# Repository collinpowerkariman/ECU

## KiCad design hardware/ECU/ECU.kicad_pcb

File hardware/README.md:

# Wiring Guide
To simplify wiring we'll set a standard wire color for each functionality.

| Color  | Description      |
|--------|------------------|
| RED    | Positive voltage |
| BLACK  | Ground voltage   |
| YELLOW | SPI - CLK        |
| WHITE  | SPI - CIPO/MISO  |
| BLUE   | SPI - COPI/MOSI  |
| GREEN  | SPI - CS         |

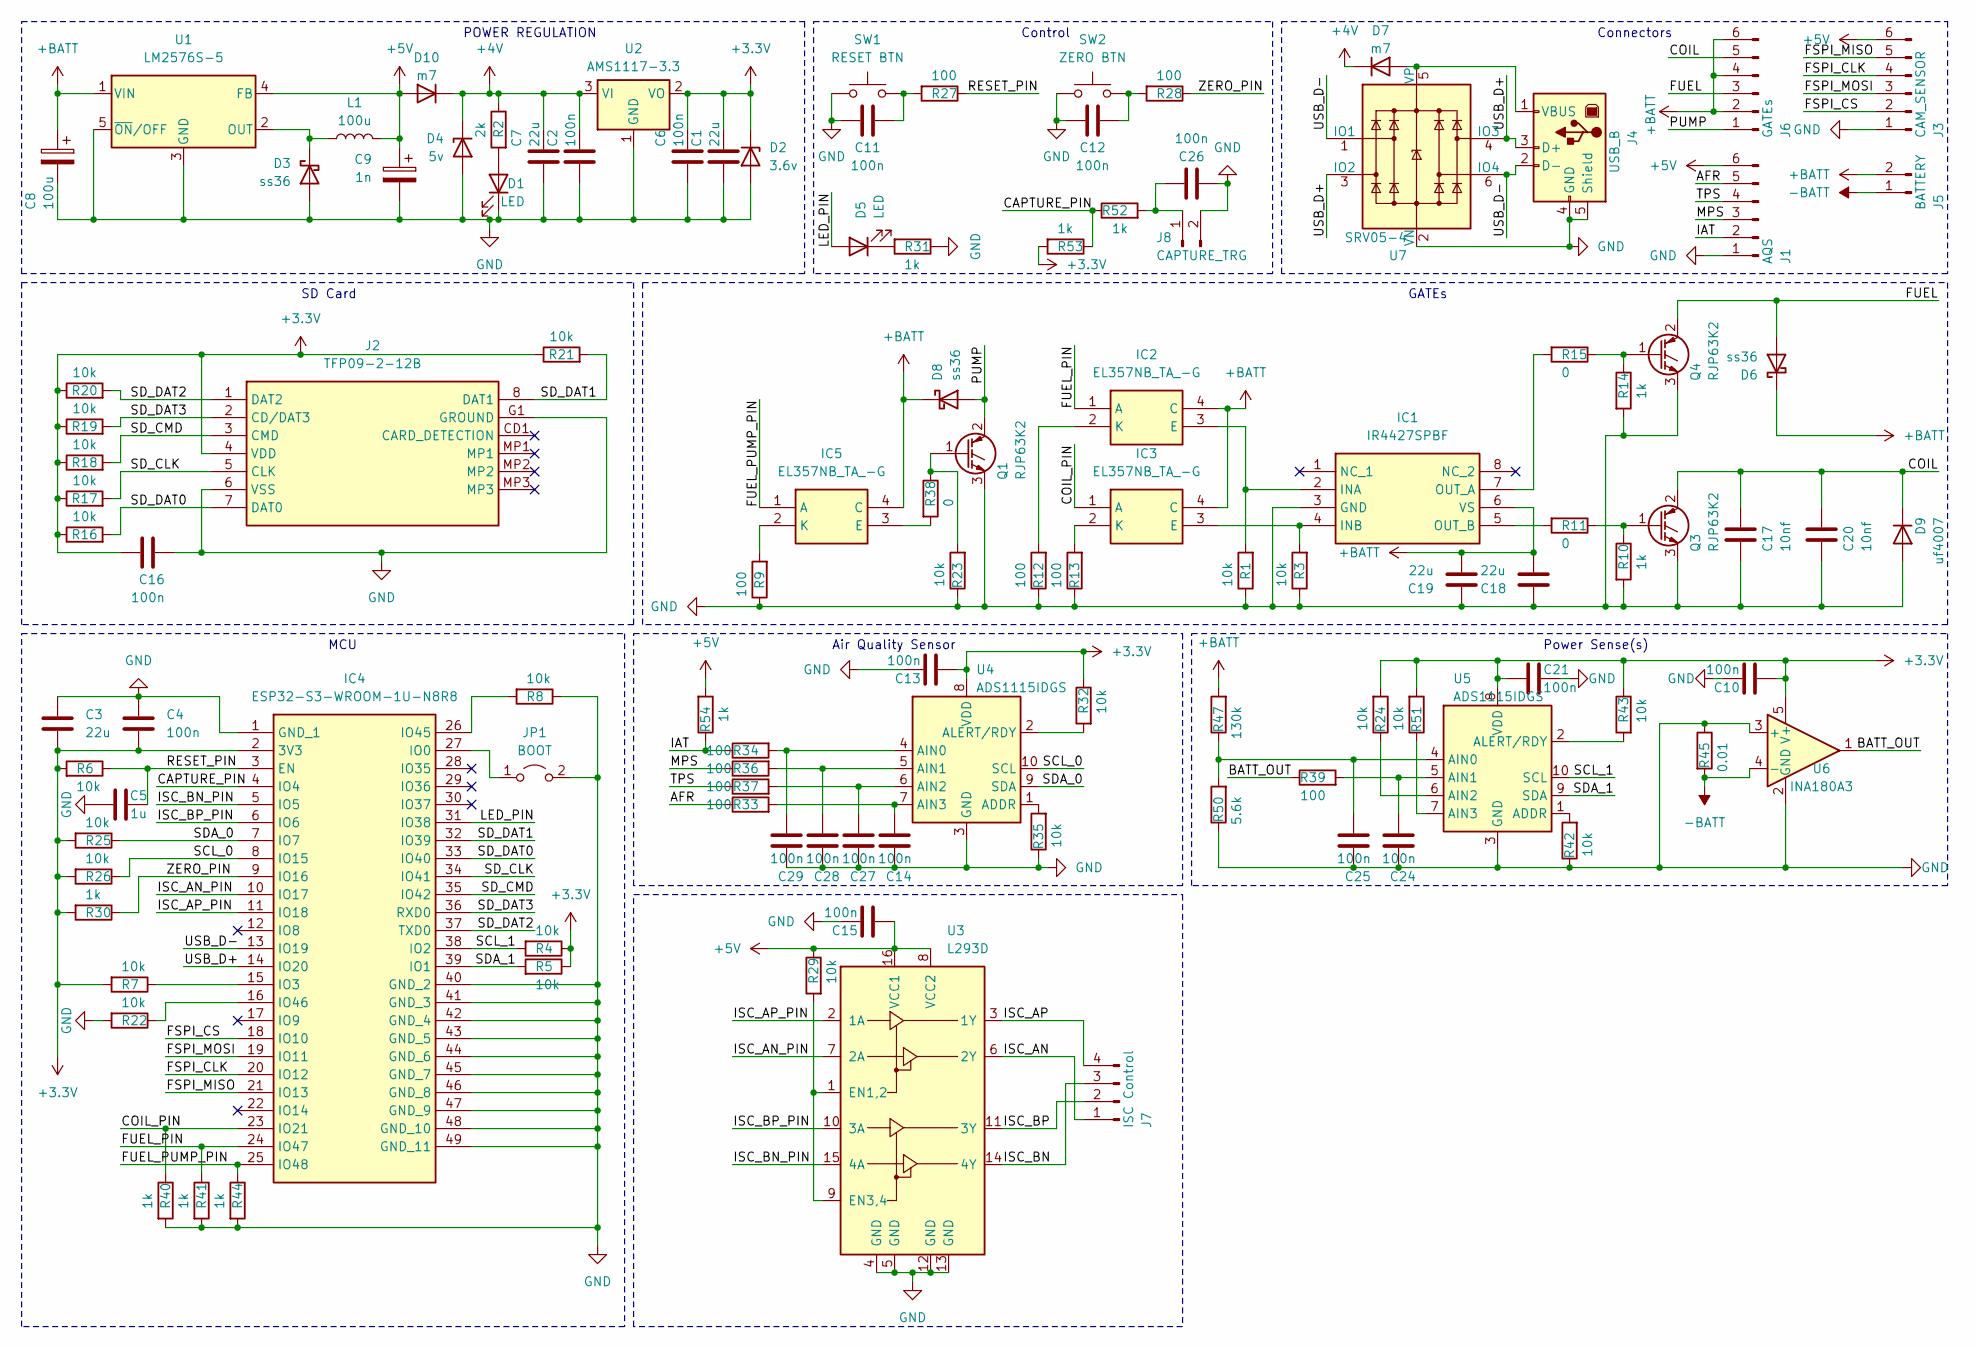
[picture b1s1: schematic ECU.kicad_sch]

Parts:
C1, C7, C18, C19: 22u; C_0805_2012Metric_Pad1.18x1.45mm_HandSolder
C2, C6: 100n; C_0805_2012Metric_Pad1.18x1.45mm_HandSolder
C3: 22u; C_0603_1608Metric
C4, C10, C11, C12, C13, C14, C15, C21, C24, C25, C26, C27, C28, C29: 100n; C_0603_1608Metric
C5: 1u; C_0603_1608Metric
C8: 100u; CP_Elec_10x10
C9: 1n; CP_Elec_10x10
C16: 100n; C_0603_1608Metric_Pad1.08x0.95mm_HandSolder
C17, C20: 10nf; C_1206_3216Metric_Pad1.33x1.80mm_HandSolder
D1, D5: LED; LED_0603_1608Metric_Pad1.05x0.95mm_HandSolder
D2: 3.6v; D_1206_3216Metric_Pad1.42x1.75mm_HandSolder
D3, D6, D8: ss36; D_SMC
D4: 5v; D_1206_3216Metric_Pad1.42x1.75mm_HandSolder
D7, D10: m7; D_SMA
D9: uf4007; D_SMA
IC1: IR4427SPBF; SOIC127P600X175-8N; Manufacturer_Part_Number IR4427SPBF; Mouser Part Number 942-IR4427SPBF
IC2, IC3, IC5: EL357NB_TA_-G; EL357NG; Manufacturer_Part_Number EL357NB(TA)-G; Mouser Part Number 638-EL357NBTAG
IC4: ESP32-S3-WROOM-1U-N8R8; ESP32S3WROOM1UN4; Manufacturer_Part_Number ESP32-S3-WROOM-1U-N8R8; Mouser Part Number 356-ESP32S3WRM1UN8R8
J1: AQS; JST_XH_B6B-XH-A_1x06_P2.50mm_Vertical
J2: TFP09-2-12B; TFP09212B; Manufacturer_Part_Number TFP09-2-12B
J3: CAM_SENSOR; JST_XH_B6B-XH-A_1x06_P2.50mm_Vertical
J4: USB_B; USB_B_TE_5787834_Vertical
J5: BATTERY; Molex_KK-396_5273-02A_1x02_P3.96mm_Vertical
J6: GATEs; Molex_KK-396_5273-06A_1x06_P3.96mm_Vertical
J7: ISC Control; JST_XH_B4B-XH-A_1x04_P2.50mm_Vertical
J8: CAPTURE_TRG; JST_XH_B2B-XH-A_1x02_P2.50mm_Vertical
JP1: BOOT; PinHeader_1x02_P2.54mm_Vertical
L1: 100u; INDPM102100X400N
Q1, Q3, Q4: RJP63K2; TO-263-2
R1, R3, R4, R5, R6, R7, R8, R22, R23, R24, R25, R26, R29, R32, R35, R42, R43, R51: 10k; R_0603_1608Metric_Pad0.98x0.95mm_HandSolder
R2: 2k; R_0603_1608Metric_Pad0.98x0.95mm_HandSolder
R9, R12, R13, R27, R28, R33, R34, R36, R37, R39: 100; R_0603_1608Metric_Pad0.98x0.95mm_HandSolder
R10, R14, R30, R31, R40, R41, R44, R52, R53, R54: 1k; R_0603_1608Metric_Pad0.98x0.95mm_HandSolder
R11, R15, R38: 0; R_0603_1608Metric_Pad0.98x0.95mm_HandSolder
R16, R17, R18, R19, R20, R21: 10k; R_0603_1608Metric
R45: 0.01; RESC10052X106N
R47: 130k; R_0603_1608Metric_Pad0.98x0.95mm_HandSolder
R50: 5.6k; R_0603_1608Metric_Pad0.98x0.95mm_HandSolder
SW1: RESET BTN; SW_SPST_PTS810
SW2: ZERO BTN; SW_SPST_PTS810
U1: LM2576S-5; TO-263-5_TabPin3
U2: AMS1117-3.3; SOT-223-3_TabPin2
U3: L293D; DIP-16_W7.62mm_SMDSocket_SmallPads
U4, U5: ADS1115IDGS; TSSOP-10_3x3mm_P0.5mm
U6: INA180A3; SOT-23-5
U7: SRV05-4; SOT-23-6

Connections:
+3.3V: C1.1, C3.2, C4.2, C6.1, C10.2, C13.2, C16.1, C21.2, D2.1 (K), IC4.2 (3V3), J2.4 (VDD), R4.1, R5.1, R6.2, R7.2, R16.1, R17.1, R18.1, R19.1, R20.1, R21.1, R24.2, R25.2, R26.2, R30.2, R32.1, R43.1, R51.2, R53.2, U2.2 (VO), U4.8 (VDD), U5.8 (VDD), U6.5 (V+)
+4V: C2.1, C7.1, D4.1 (K), D7.1 (K), D10.1 (K), R2.1, U2.3 (VI)
+5V: C9.1, C15.2, D10.2 (A), J1.6, J3.6, L1.2, R29.1, R54.2, U1.4 (FB), U3.8 (VCC2), U3.16 (VCC1)
+BATT: C8.1, C18.1, C19.1, D6.1 (K), D8.1 (K), IC1.6 (VS), IC2.4 (C), IC3.4 (C), IC5.4 (C), J5.2, J6.2, J6.4, J6.6, R47.2, U1.1 (VIN)
-BATT: J5.1, R45.2, U6.4 (-)
/AFR: J1.5, R33.1
/BATT_OUT: R39.1, U6.1
/CAPTURE_PIN: IC4.4 (IO4), R52.1, R53.1
/COIL: C17.1, C20.1, D9.1 (K), J6.5, Q3.2 (C)
/COIL_PIN: IC3.1 (A), IC4.23 (IO21), R40.1
/FSPI_CLK: IC4.20 (IO12), J3.4
/FSPI_CS: IC4.18 (IO10), J3.2
/FSPI_MISO: IC4.21 (IO13), J3.5
/FSPI_MOSI: IC4.19 (IO11), J3.3
/FUEL: D6.2 (A), J6.3, Q4.2 (C)
/FUEL_PIN: IC2.1 (A), IC4.24 (IO47), R41.1
/FUEL_PUMP_PIN: IC4.25 (IO48), IC5.1 (A), R44.1
/IAT: J1.2, R34.1, R54.1
/ISC_AN: J7.1, U3.6 (2Y)
/ISC_AN_PIN: IC4.10 (IO17), U3.7 (2A)
/ISC_AP: J7.4, U3.3 (1Y)
/ISC_AP_PIN: IC4.11 (IO18), U3.2 (1A)
/ISC_BN: J7.3, U3.14 (4Y)
/ISC_BN_PIN: IC4.5 (IO5), U3.15 (4A)
/ISC_BP: J7.2, U3.11 (3Y)
/ISC_BP_PIN: IC4.6 (IO6), U3.10 (3A)
/LED_PIN: D5.2 (A), IC4.31 (IO38)
/MPS: J1.3, R36.1
/PUMP: D8.2 (A), J6.1, Q1.2 (C)
/RESET_PIN: C5.2, IC4.3 (EN), R6.1, R27.1
/SCL_0: IC4.8 (IO15), R26.1, U4.10 (SCL)
/SCL_1: IC4.38 (IO2), R4.2, U5.10 (SCL)
/SDA_0: IC4.7 (IO7), R25.1, U4.9 (SDA)
/SDA_1: IC4.39 (IO1), R5.2, U5.9 (SDA)
/SD_CLK: IC4.34 (IO41), J2.5 (CLK), R17.2
/SD_CMD: IC4.35 (IO42), J2.3 (CMD), R18.2
/SD_DAT0: IC4.33 (IO40), J2.7 (DAT0), R16.2
/SD_DAT1: IC4.32 (IO39), J2.8 (DAT1), R21.2
/SD_DAT2: IC4.37 (TXD0), J2.1 (DAT2), R20.2
/SD_DAT3: IC4.36 (RXD0), J2.2 (CD/DAT3), R19.2
/TPS: J1.4, R37.1
/USB_D+: IC4.14 (IO20), J4.3 (D+), U7.3 (IO2), U7.4 (IO3)
/USB_D-: IC4.13 (IO19), J4.2 (D-), U7.1 (IO1), U7.6 (IO4)
/ZERO_PIN: IC4.9 (IO16), R28.1, R30.1
GND: C1.2, C2.2, C3.1, C4.1, C5.1, C6.2, C7.2, C8.2, C9.2, C10.1, C11.1, C12.1, C13.1, C14.1, C15.1, C16.2, C17.2, C18.2, C19.2, C20.2, C21.1, C24.1, C25.1, C26.1, C27.1, C28.1, C29.1, D1.1 (K), D2.2 (A), D3.2 (A), D4.2 (A), D9.2 (A), IC1.3 (GND), IC4.1 (GND_1), IC4.40 (GND_2), IC4.41 (GND_3), IC4.42 (GND_4), IC4.43 (GND_5), IC4.44 (GND_6), IC4.45 (GND_7), IC4.46 (GND_8), IC4.47 (GND_9), IC4.48 (GND_10), IC4.49 (GND_11), J1.1, J2.6 (VSS), J2.G1 (GROUND), J3.1, J4.4 (GND), J4.5 (Shield), J8.2, JP1.2 (B), Q1.3 (E), Q3.3 (E), Q4.3 (E), R1.1, R3.1, R8.1, R9.1, R10.2, R12.1, R13.1, R14.2, R22.2, R23.1, R31.1, R35.1, R40.2, R41.2, R42.1, R44.2, R45.1, R50.1, SW1.1, SW2.1, U1.3 (GND), U1.5 (~ON/OFF), U2.1 (GND), U3.4 (GND), U3.5 (GND), U3.12 (GND), U3.13 (GND), U4.3 (GND), U5.3 (GND), U6.2 (GND), U6.3 (+), U7.2 (VN)
unnamed: C11.2, R27.2, SW1.2
unnamed: C12.2, R28.2, SW2.2
unnamed: D1.2 (A), R2.2
unnamed: D3.1 (K), L1.1, U1.2 (OUT)
unnamed: D5.1 (K), R31.2
unnamed: D7.2 (A), J4.1 (VBUS), U7.5 (VP)
unnamed: IC1.2 (INA), IC2.3 (E), R1.2
unnamed: IC1.4 (INB), IC3.3 (E), R3.2
unnamed: IC1.7 (OUT_A), R15.2
unnamed: IC1.5 (OUT_B), R11.2
unnamed: IC2.2 (K), R12.2
unnamed: IC3.2 (K), R13.2
unnamed: IC4.27 (IO0), JP1.1 (A)
unnamed: IC4.15 (IO3), R7.1
unnamed: IC4.26 (IO45), R8.2
unnamed: IC4.16 (IO46), R22.1
unnamed: IC5.3 (E), R38.2
unnamed: IC5.2 (K), R9.2
unnamed: C26.2, J8.1, R52.2
unnamed: Q1.1 (G), R23.2, R38.1
unnamed: Q3.1 (G), R10.1, R11.1
unnamed: Q4.1 (G), R14.1, R15.1
unnamed: R29.2, U3.1 (EN1,2), U3.9 (EN3,4)
unnamed: R35.2, U4.1 (ADDR)
unnamed: C29.2, R34.2, U4.4 (AIN0)
unnamed: C28.2, R36.2, U4.5 (AIN1)
unnamed: C27.2, R37.2, U4.6 (AIN2)
unnamed: C14.2, R33.2, U4.7 (AIN3)
unnamed: R32.2, U4.2 (ALERT/RDY)
unnamed: R42.2, U5.1 (ADDR)
unnamed: C25.2, R47.1, R50.2, U5.4 (AIN0)
unnamed: C24.2, R39.2, U5.5 (AIN1)
unnamed: R24.1, U5.6 (AIN2)
unnamed: R51.1, U5.7 (AIN3)
unnamed: R43.2, U5.2 (ALERT/RDY)

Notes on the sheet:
POWER REGULATION
Connectors
Power Sense(s)
MCU
GATEs
Control
SD Card
Air Quality Sensor

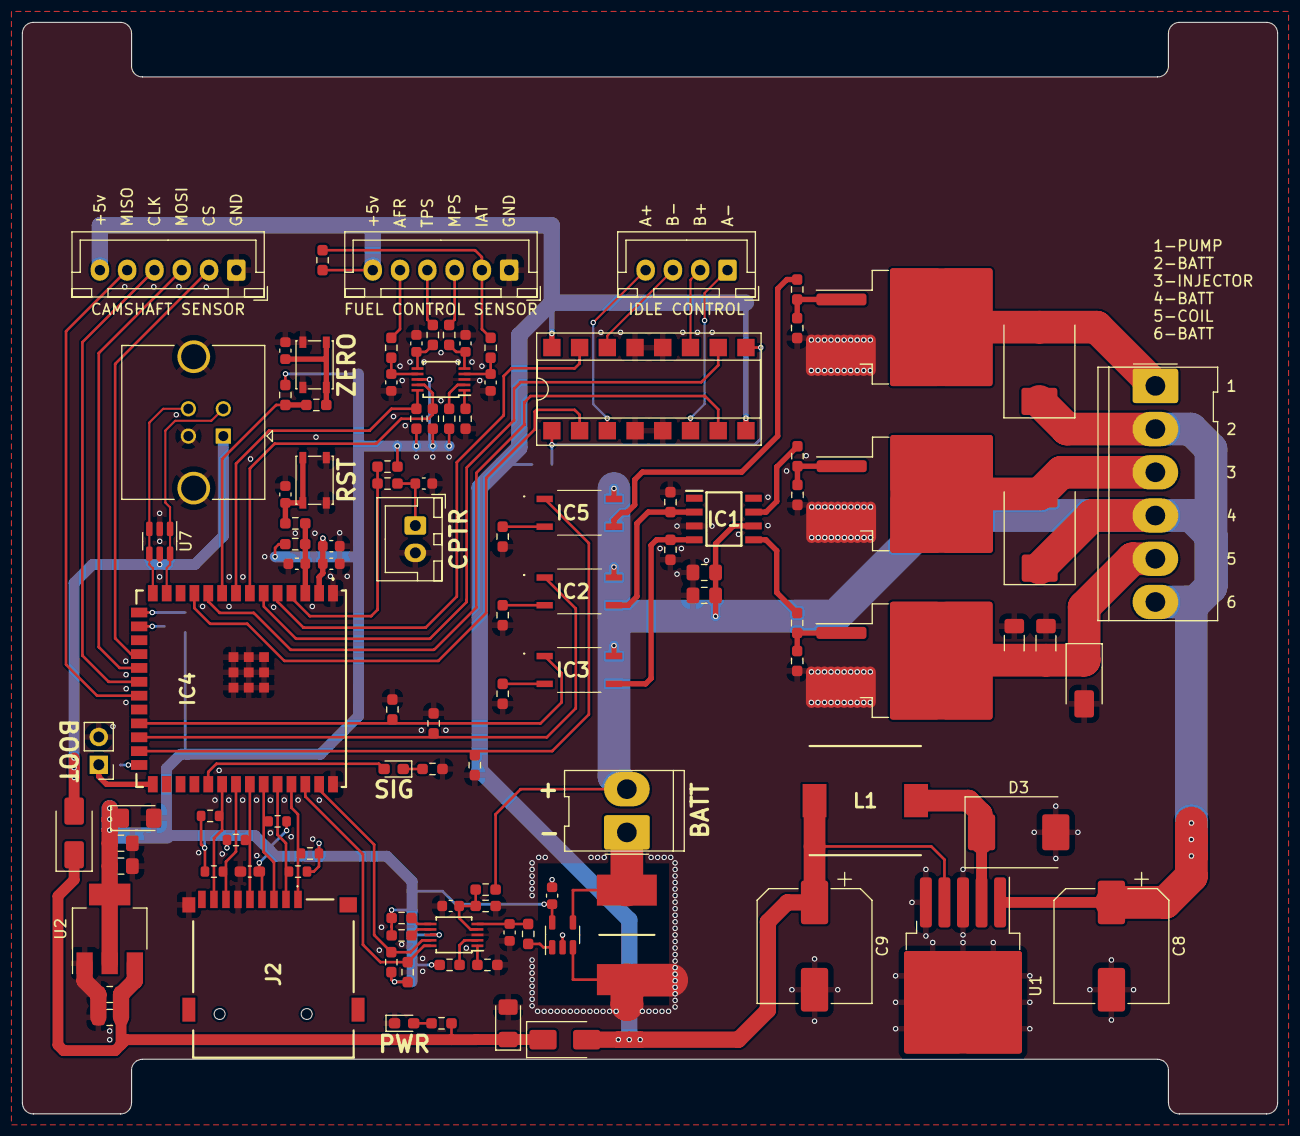
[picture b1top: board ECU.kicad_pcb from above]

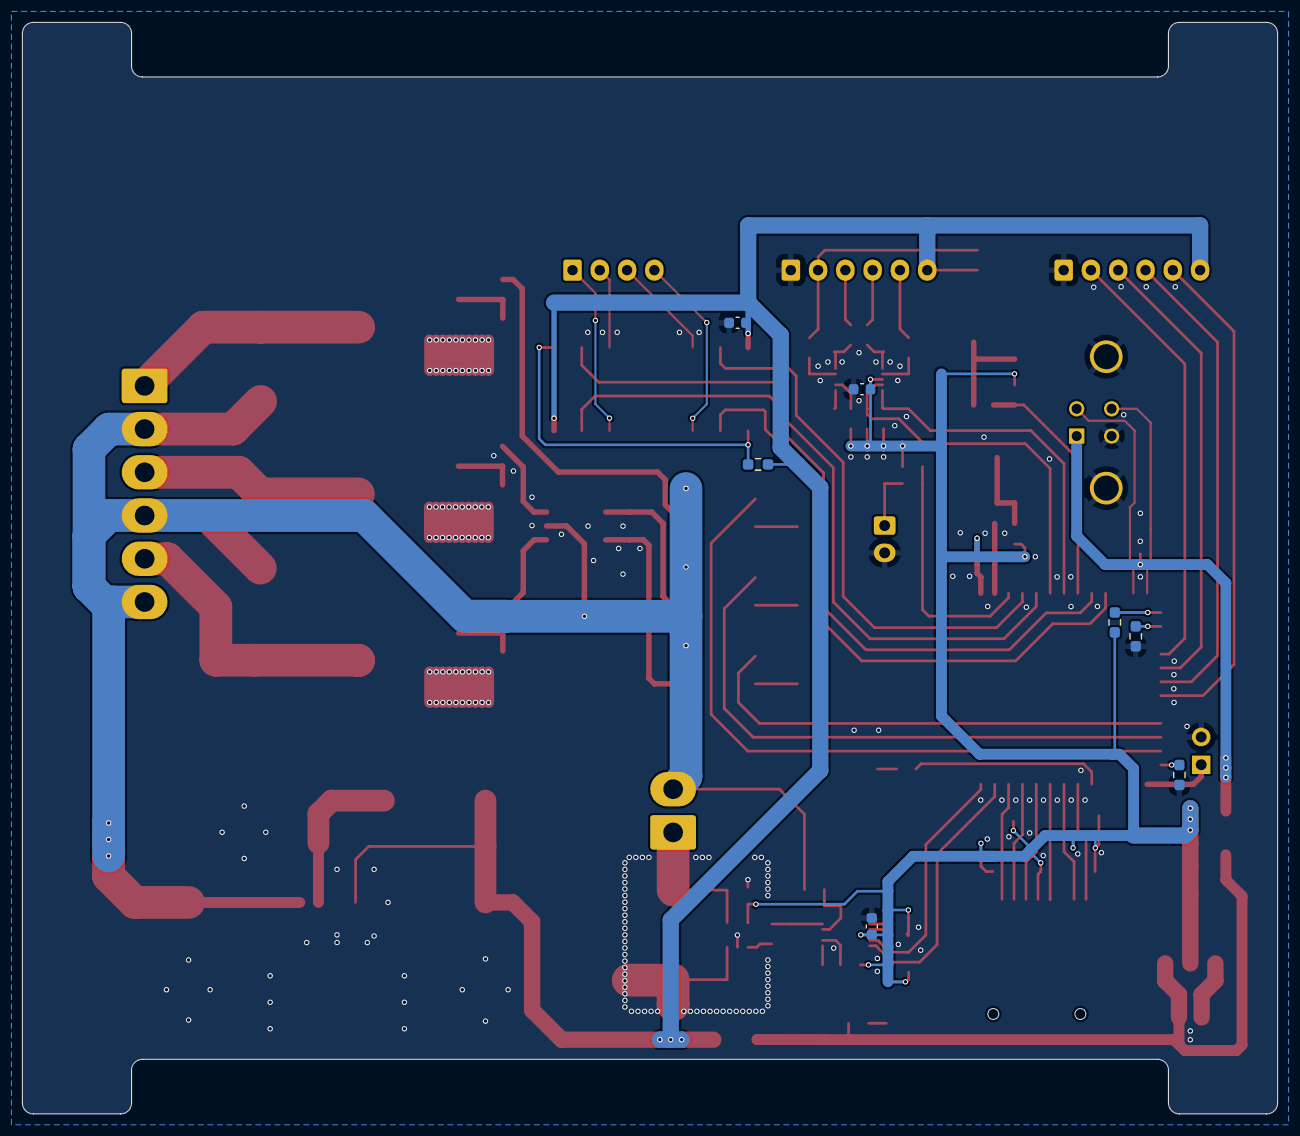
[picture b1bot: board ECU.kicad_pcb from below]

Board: 2 copper layers, 115.0 x 100.0 mm, 115 parts (7 on the bottom side), 80 nets.

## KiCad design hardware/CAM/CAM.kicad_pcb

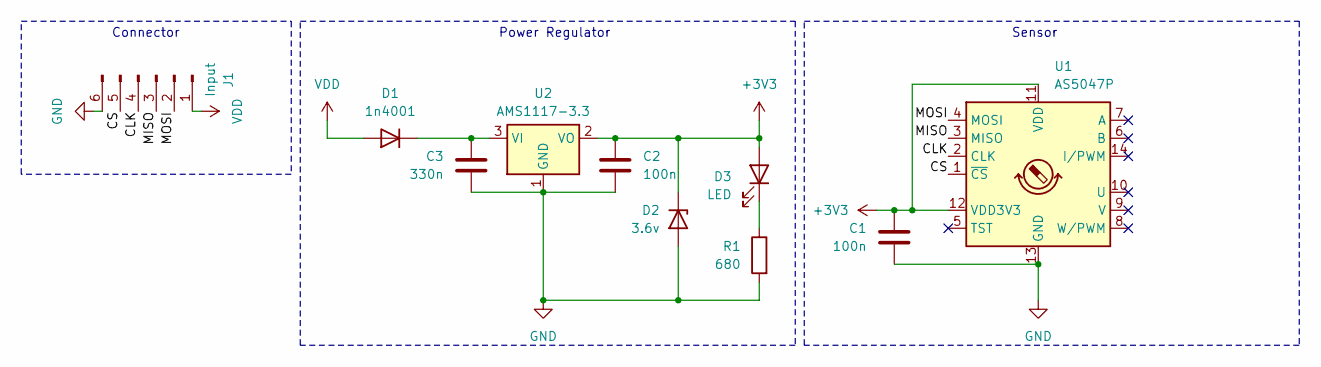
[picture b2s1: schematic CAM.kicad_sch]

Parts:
C1, C2: 100n; C_0603_1608Metric
C3: 330n; C_0603_1608Metric
D1: 1n4001; D_SMA
D2: 3.6v; D_MiniMELF
D3: LED; D_0603_1608Metric
J1: Input; 6P_Board_To_Wire_Pad
R1: 680; R_0603_1608Metric
U1: AS5047P; TSSOP-14_4.4x5mm_P0.65mm
U2: AMS1117-3.3; SOT-223-3_TabPin2

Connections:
+3V3: C1.1, C2.1, D2.1 (K), D3.2 (A), U1.11 (VDD), U1.12 (VDD3V3), U2.2 (VO)
/CLK: J1.4, U1.2 (CLK)
/CS: J1.5, U1.1 (~CS)
/MISO: J1.3, U1.3 (MISO)
/MOSI: J1.2, U1.4 (MOSI)
GND: C1.2, C2.2, C3.2, D2.2 (A), J1.6, R1.2, U1.13 (GND), U2.1 (GND)
unnamed: C3.1, D1.1 (K), U2.3 (VI)
unnamed: D3.1 (K), R1.1
VDD: D1.2 (A), J1.1

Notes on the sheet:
Power Regulator
Sensor
Connector

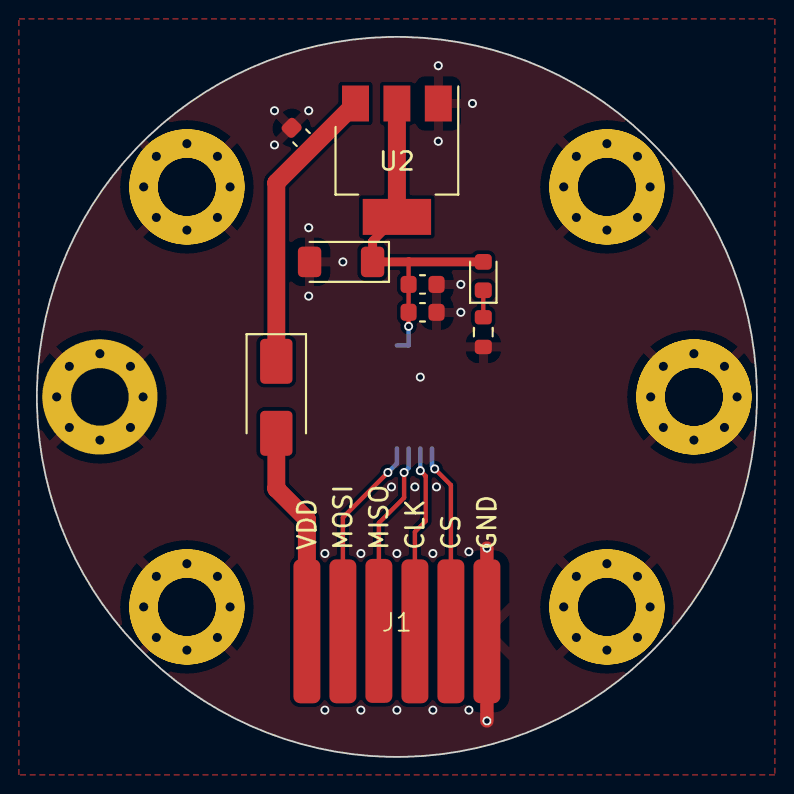
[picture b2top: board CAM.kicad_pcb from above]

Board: 2 copper layers, 40.0 x 40.0 mm, 10 parts (1 on the bottom side), 9 nets.

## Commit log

2023-10-10 simplify camshaft sensor schematic and add extra mounting hole
2023-10-30 backup
2023-11-06 ECU hardware v0.2 candidate
2023-11-08 add idle control circuit
2023-11-11 fix gerber file containing deleted layers
